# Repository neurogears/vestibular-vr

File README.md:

# vestibular-vr
Closed-loop VR setup for Rancz Lab

[Design Document](https://github.com/neurogears/vestibular-vr/blob/main/Design%20Documents/Vestibular%20VR%20Design%20Document.md)

### Acquisition Prerequisites

The following need to be installed on a fresh system in order to bootstrap the Bonsai environment correctly:

* Windows 10 or greater
* [Visual Studio Code](https://code.visualstudio.com/) (recommended for editing code scripts and git commits)
* [.NET 8.0 SDK](https://dotnet.microsoft.com/en-us/download/dotnet/8.0)
* [.NET Framework 4.7.2 Developer Pack](https://dotnet.microsoft.com/download/dotnet-framework/thank-you/net472-developer-pack-offline-installer) (required for intellisense when editing code scripts)
* [Git for Windows](https://gitforwindows.org/) (recommended for cloning and manipulating this repository)
* [Visual C++ Redistributable for Visual Studio 2012](https://www.microsoft.com/en-us/download/details.aspx?id=30679) (native dependency for OpenCV)
* [FTDI CDM Driver 2.12.28](https://www.ftdichip.com/Drivers/CDM/CDM21228_Setup.zip) (serial port drivers for HARP devices)
* [Spinnaker SDK 1.29.0.5](https://www.teledynevisionsolutions.com/support/support-center/software-firmware-downloads/iis/spinnaker-sdk-download/spinnaker-sdk--download-files) (device drivers for FLIR cameras, sign in required, look in the archived stable versions for 1.29.0.5)

### Setting up the Bonsai environment

To set up a Bonsai environment for running vestibular-vr, use the terminal to clone the repo into a local folder:

``` 
git clone https://github.com/neurogears/vestibular-vr.git
```

Now navigate into vestibular-vr/bonsai folder and run the `Setup.ps1` script (on Windows right-click > Run with powershell). Once all dependencies have been restored Bonsai can be launched in a local environment from the `.exe` in this folder.

### Session settings

Experiment parameters are based on a json schema (`schema.json` in the repo). Implementations of this schema are defined in `.yml` files provided by the user that are then loaded in the main Bonsai workflow to set up experiment parameters.

#### Working with schemas in Visual Studio Code
To create and edit schema implementations with full autcomplete and hinting, Visual Studio Code requires some extensions to be added:
* json (ZainChen.json)
* JSON Schema Validator (tberman.json-schema-validator)
* YAML (redhat.vscode-yaml)

#### Creating an experiment parameter file
To create an experiment parameter file based on the `schema`, create a new `.yml` file and add a reference to the `schema` at the top of the file

```
%YAML 1.1
---
# yaml-language-server: $schema=schema.json
```

The `schema` has two main groups of properties that define global experiment parameters, and block-specific parameters respectively, e.g.:

```
metadata:
  animalId: plimbo
  rootPath: D:/TrialLogicTestData/
  runGain: 0.0005

blocks: [
  &blockA
  {
    stimulus: {type: "grating"},
    totalRuntime: 20,
    runThreshold: 100,
    decayTimestep: 0.1,
    runThresholdDecay: -1,
    haltProbability: 0.5,
    haltProtocol: {
      minumumDelay: 0.1,
      randomDelay: 1.5,
      haltTime: 2,
      haltGain: 0
    }
  },
  &blockB
  {
    stimulus: {type: "cloud"},
    totalRuntime: 140,
    runThreshold: 200,
    decayTimestep: 0.1,
    runThresholdDecay: -1,
    haltProbability: 0.7,
    haltProtocol: {
      minumumDelay: 0.1,
      randomDelay: 0.5,
      haltTime: 0.5,
      haltGain: 0
    }
  },
  {<<: *blockA},
  {<<: *blockB}
]
```

The description of each parameter's effect on the Bonsai workflow, along with its type and default values are defined within `schema.json` itself. Note that where a parameter is not specifically set in the `.yml` the value will revert the default.

### Running an experiment
To run an experiment, run the Bonsai application from the local environment and open Main.bonsai. Use the property grid to select the desired experiment parameter `.yml` file.

### Gain settings
The `schema` has a number of gain settings that can be used to flexibly the define the relationship between real-time data sources (ball movement, encoder reading, file playback) and closed-loop outputs like visual field movement or motor movement. These gains are applied hierarchically with some affecting all calculations, and some defined per-block or per-source:

- `runGain` - global gain applied to all calculations
  - `blockGainModifier` - additional gain specific to a block
    - Visual: gains that contribute to visual field motion
      - `flowXToVisualGain` - gain applied to optical sensor X reading
      - `flowYToVisualGain` - gain applied to optical sensor Y reading
      - `rotaryToVisualGain` - gain applied to the rotary encoder reading
      - `playbackToVisualGain` - gain applied to the file playback data source
    - Motor: gains that contribute to motor motion
      - `flowXToMotorGain` - gain applied to optical sensor X reading
      - `flowYToMotorGain` - gain applied to optical sensor Y reading
      - `playbackToMotorGain` - gain applied to the file playback data source
  - `haltGain` - set as part of a `haltProtocol`. Applies a gain to all sources during a halt, block-specific.

We use the term 'procession' to describe the movement delta of the visual field or motor in response to an update from a data source (optical flow, playback etc.) on a given trial. Let `h` be a variable that describes whether a halt is currently happening (1 = halt happening, 0 = halt not happening), visual and motor processions are defined as:

```
visualProcession = (runGain * blockGainModifier) * (flowXToVisualGain*flowX + flowYToVisualGain*flowY + rotaryToVisualGain*encoder + playbackToVisualGain*playback) * (haltGain*h)
```
```
motorProcession = (runGain * blockGainModifier) * (flowXToMotorGain*flowX + flowYToMotorGain*flowY + playbackToVisualGain*playback) * (haltGain*h)
```

`motorProcession` is converted by the function `ToPulseInterval` to an immediate pulse interval command which is written to the motor. The conversion between this command and the speed of the motor is dependent on the hardware settings for pulse interval --> motor motion on the motor controller.
The relationship of `visualProcession` to visual field movement is dependent on the current visual stimulus being presented. For example for a gratings stimulus, the value represents the absolute phase angle of the gratings being shown. For a motion clouds stimulus, it represents the (wrapped) index of the motion cloud frame being shown.

Gains can be set to modify the contribution of a data source to procession, for example to specify a block where visual motion is only dependent on the X value of the flow sensor we can set:

```
# metadata
runGain: 0.0008 # represents final conversion from procession to visual angle
# block settings
blockGainModifier: 1 # block modifier does not scale input data sources
flowXToVisualGain: 1 # we want the X flow value to contribute
flowYToVisualGain: 0 # we don't want the Y flow value to contribute
rotaryToVisualGain: 0 # encoder reading should not contribute
playbackToVisualGain: 0 # playback source should not contribute
```

### Optical flow sensor smoothing

An average smoothing function is applied to the optical sensor reading. A `schema` parameter `flowSmoothing` is applied per-block which specifies a count of how many samples to smooth over, i.e. the length of the buffer to take an average, smoothed value from.

### Data logging
Data is logged according to the [Aeon.Acquisition](https://github.com/SainsburyWellcomeCentre/aeon_acquisition) format. Generally, data is grouped according to a folder named with a timestamp representing the start time of an experiment. Within this folder, data is organised by **device**, where a device may be a camera, Harp board, ONIX acquisition etc. For longer experiments, data is 'chunked' by hour such that the full raw data is split across multiple files to ensure no single file grows unmanageably large.

Within each device, data may be stored in a different format according to the device's data output. In general however, there will be a log of the raw data (e.g. camera frames, sensor readings) and a corresponding source of timestamps to allow for relating the data to the Harp clock. For a camera, this will take the form of a video file with the acquired camera frames, as well as a corresponding .csv file with paired Harp timestamps and camera frame indices. For a Harp device, this will take the form of a flat binary file organised by individual register, with the output of that register paired with a Harp timestamp.

As Harp files are saved as flat binary, it is recommended to use the device schema for that Harp device to parse the individual values and read the correct data type.

### Python environment

The following need to be installed once on a new system in order to analyze data:

 * [Visual Studio Code](https://code.visualstudio.com/) (recommended for editing code scripts and git commits)
 * A Conda distribution such as [Miniconda](https://docs.anaconda.com/free/miniconda/index.html)
 * [Python Extension for VS Code](https://marketplace.visualstudio.com/items?itemName=ms-python.python)
   * This extension needs to be made aware of the Conda installation. To do so, navigate to the extension settings. Under the section **Python: Conda Path**, enter the full path to the conda.bat executable. ([more info](https://stackoverflow.com/a/77615160/3312269).)
 * [Jupyter Extension for VS Code](https://marketplace.visualstudio.com/items?itemName=ms-toolsai.jupyter)

#### Create local Environment
1. Open the vestibular-vr folder in VS Code
2. `Ctrl+Shift+P` in VS Code > Python: Create Environment
   * Select Conda
   * Select Python 3.11 kernel
3. Ensure pip is upgraded:
 ```
 pip install --upgrade pip
 ```
4. From the terminal run `pip install -r requirements.txt`
5. Clone aeon_mecha into a separate directory 
 ```
 git clone https://github.com/SainsburyWellcomeCentre/aeon_mecha.git 
 ```
6. From the VS Code terminal, `cd` into the aeon_mecha directory and run:
 ```
 python -m pip install -e .
 ```

 ### SLEAP
 Follow the standard instructions for [installing SLEAP](https://sleap.ai/installation.html), [creating a project](https://sleap.ai/tutorials/new-project.html) and [labeling](https://sleap.ai/tutorials/initial-labeling.html). Ensure that you use training videos of the same pixel width and height that you will use for inference later. During training, ensure you select `single animal` as the training pipeline type, and that the image is converted to grayscale.

 After completing training, activate the sleap conda environment (if not already activated) and run:

 ```
sleap-export -m /model/folder/path
 ```

 to export the trained model to a format that can be used by Bonsai.

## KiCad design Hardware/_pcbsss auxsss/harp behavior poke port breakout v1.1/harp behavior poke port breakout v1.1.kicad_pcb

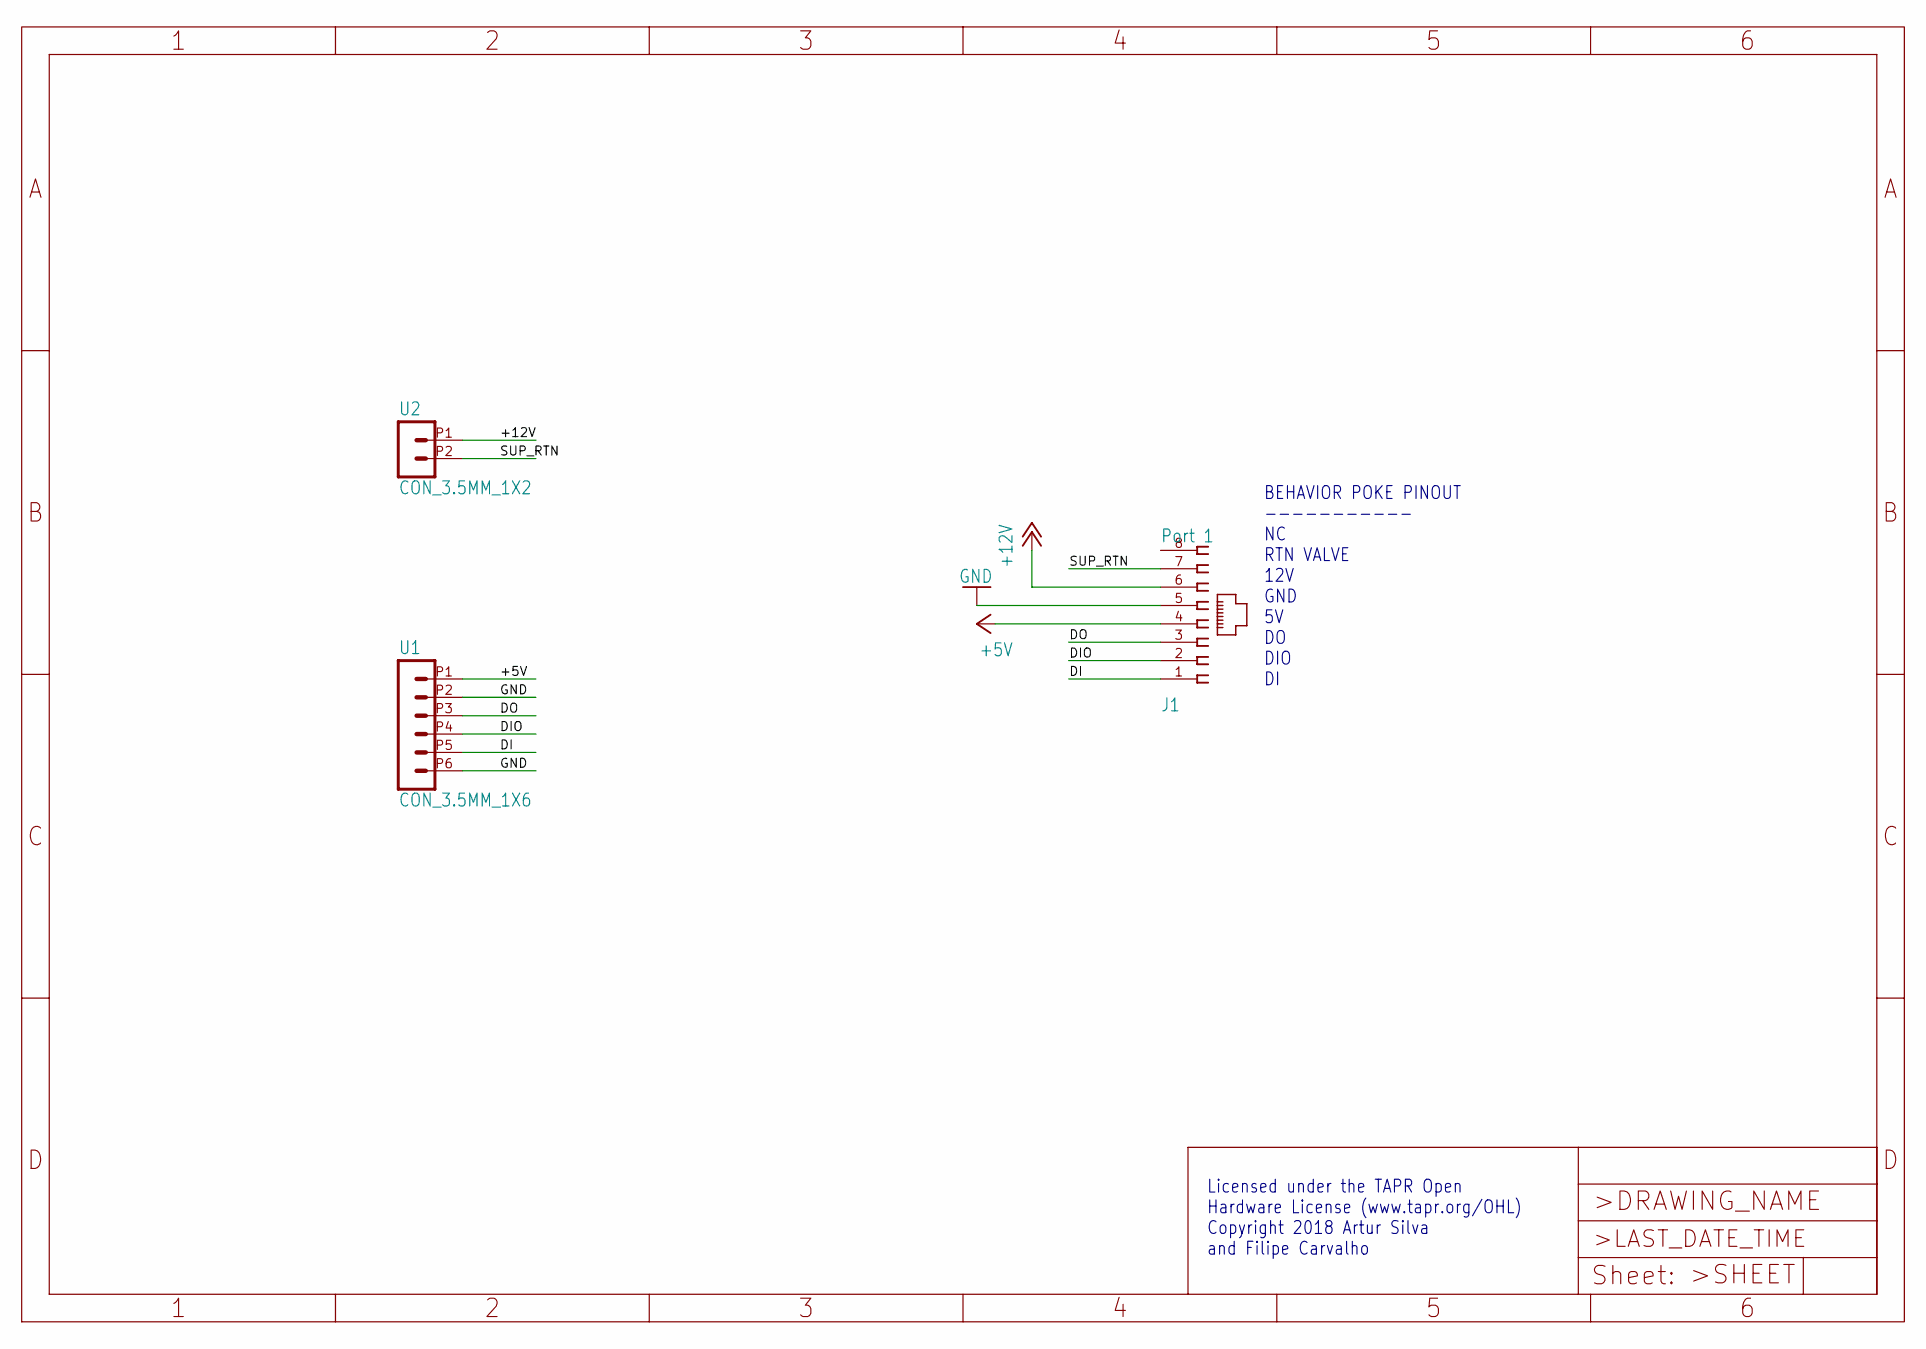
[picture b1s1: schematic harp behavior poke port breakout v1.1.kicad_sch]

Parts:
J1: Port 1; 520426-4
U1: CON_3.5MM_1X6
U2: CON_3.5MM_1X2

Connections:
+5V: J1.4, U1.P1 (1)
+12V: J1.6, U2.P1 (1)
DI: J1.1, U1.P5 (5)
DIO: J1.2, U1.P4 (4)
DO: J1.3, U1.P3 (3)
GND: J1.5, U1.P2 (2), U1.P6 (6)
SUP_RTN: J1.7, U2.P2 (2)

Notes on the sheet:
BEHAVIOR POKE PINOUT ----------- NC RTN VALVE 12V GND 5V DO DIO DI
Licensed under the TAPR Open Hardware License (www.tapr.org/OHL) Copyright 2018 Artur Silva and Filipe Carvalho

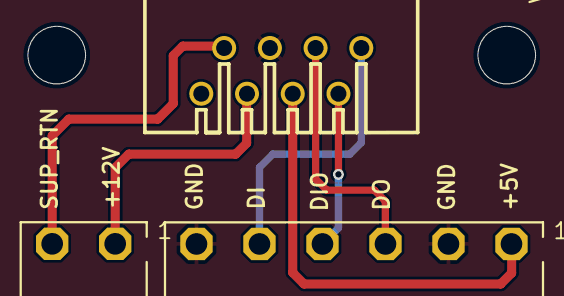
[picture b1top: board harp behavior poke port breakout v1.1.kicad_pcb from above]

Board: 2 copper layers, 6 parts (0 on the bottom side), 7 nets.

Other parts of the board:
@HOLE0, @HOLE1: (no value)
U$2: LOGO_8

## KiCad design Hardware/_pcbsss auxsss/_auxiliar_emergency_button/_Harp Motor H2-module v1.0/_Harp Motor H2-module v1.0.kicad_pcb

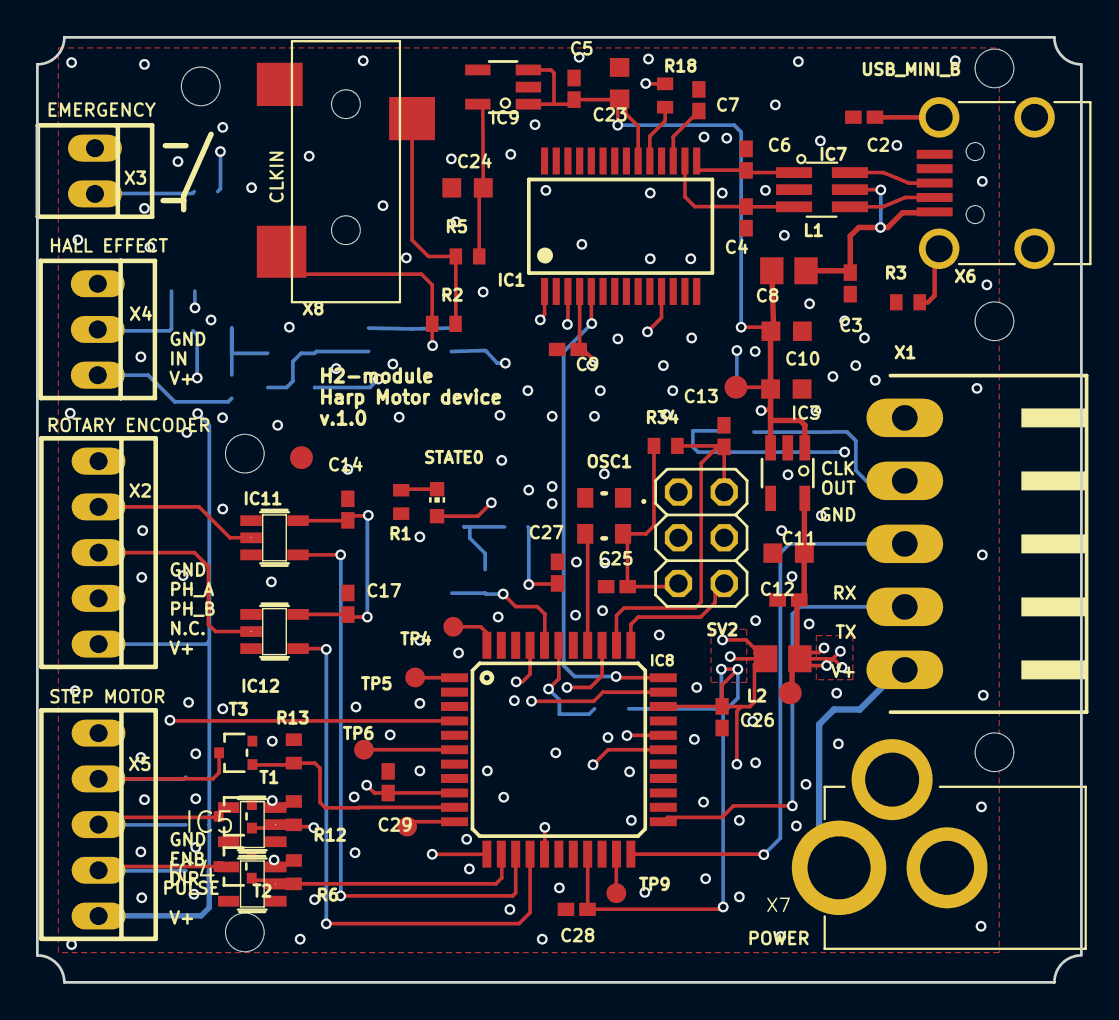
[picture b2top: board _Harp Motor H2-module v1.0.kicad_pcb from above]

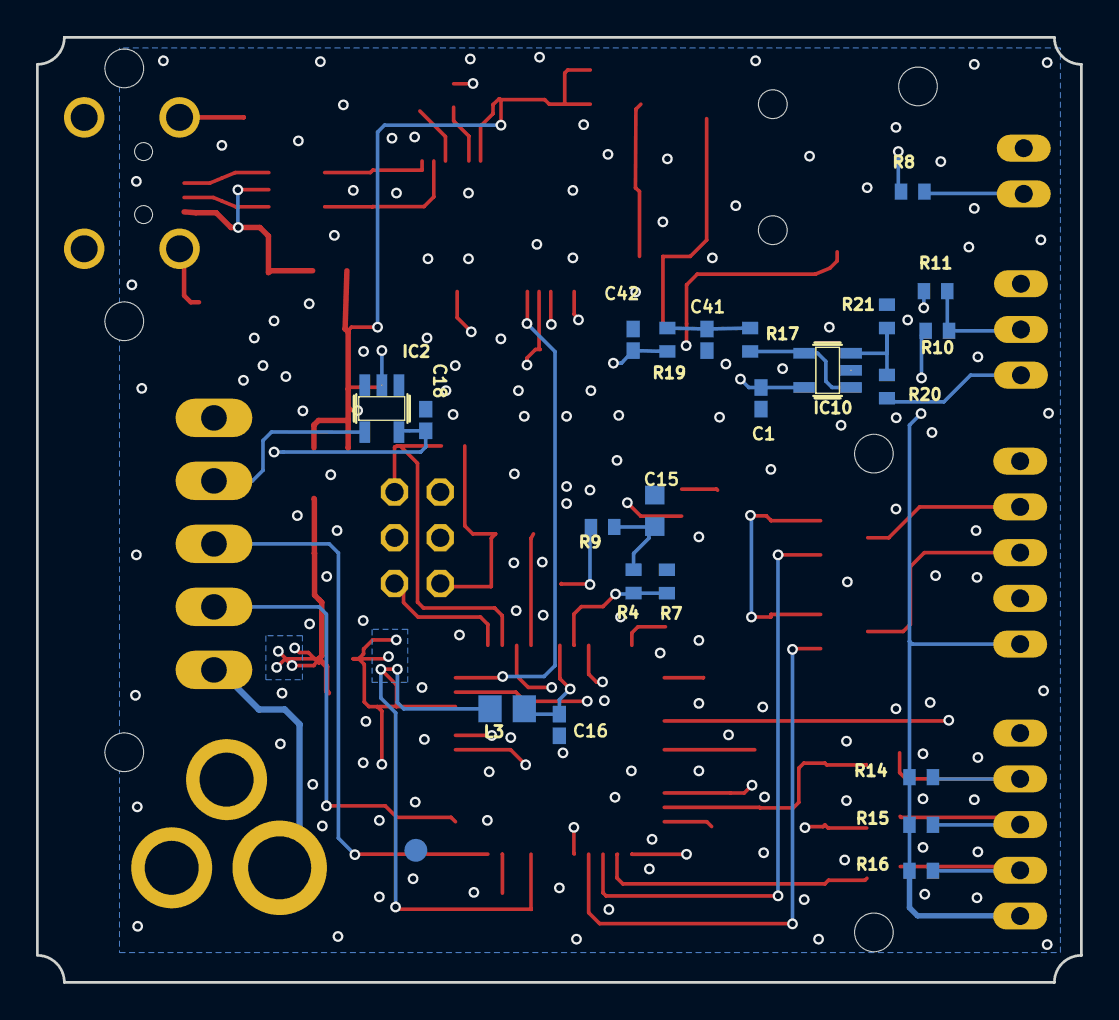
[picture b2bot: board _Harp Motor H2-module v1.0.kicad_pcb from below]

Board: 4 copper layers, 58.0 x 52.5 mm, 92 parts (23 on the bottom side), 54 nets.

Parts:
@HOLE0, @HOLE1, @HOLE2, @HOLE3, @HOLE4, @HOLE5: (no value)
C1, C3, C5, C7, C9, C12, C14, C16, C17, C18, C25, C26, C27, C28, C29: 100nF; C0402K
C2: 4.7nF; C0402K
C4, C6, C13: 47pF; C0402K
C8, C10, C11, C23, C24: 4.7uF; C0603K
C15: DNI 4.7uF; C0603K
C41, C42: 15nF 5%; C0402K
IC1: FT232RL; SSOP28
IC2, IC4, IC5, IC11, IC12: SN74LVC1G125DBVT; SOT23-5
IC3, IC9: LP5907MFX-3.3; TSOT23-5
IC7: USBLC6-2SC6; SOT23-6L
IC8: ATXMEGA32A4U; TQFP44
IC10: THS4281DBVT; SOT23-5
L1, L2, L3: 40R@100MHz; R0805
OSC1: OSCILLATOR; OSCILLATOR_3.2X2.5
R1: 330R; R0402
R2, R6, R8, R12, R13, R17, R18, R19, R34: 10k; R0402
R3: 1M; R0402
R4, R7, R14, R15, R16: DNI; R0402
R5: 10R; R0402
R9: DNI 100R; R0402
R10: DNI 0R; R0402
R11: 0R; R0402
R20: 24k; R0402
R21: 15k; R0402
STATE0: GREEN_LED; CHIP-LED0603
SV2: PINHD-2X3; 2X03
T1, T2, T3: DMG1012UW; SOT323
TP1, TP10, TP11, TP13: NO_COMPONENT; B1,27
TP4, TP5, TP6, TP8, TP9: NO_COMPONENT; TP11R
X1: 1x5 MAIN PLUG; 90G-5
X2, X5: 1x5 case; 22-23-2051
X3: 1x2 case; 22-23-2021
X4: 1x3 case; 22-23-2031
X6: USB_MINI_B; 240-0002-1
X7: DC_JACK2.1MM; DC_POWER_INPUT_2.1MM
X8: CLCK_JACK; 35RASMT2BHNTRX

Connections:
+3V3: C1.1, C9.1, C11.1, C12.1, C14.1, C17.1, C18.1, IC1.4, IC2.5, IC3.5, IC10.5, IC11.5, IC12.5, L2.2, R11.2, R18.1, TP1.TP
+5V: C5.1, C8.1, C10.1, C23.1, IC1.20, IC3.1, IC3.3, IC4.5, IC5.5, IC9.1, IC9.3, L1.1, R10.2, R14.2, R15.2, R16.2, TP13.TP, X2.5, X5.5
AREF: IC8.40, R4.1, R7.2
EMERGENCY_INPUT: IC8.4, R8.1, X3.2
FTDI_CTS: IC1.11, IC8.29
FTDI_RTS: IC1.3, IC8.28
FTDI_RXD: IC1.5, IC8.33
FTDI_TXD: IC1.1, IC8.32
GND: C1.2, C2.2, C3.2, C4.2, C5.2, C6.2, C7.2, C8.2, C9.2, C10.2, C11.2, C12.2, C13.2, C14.2, C15.2, C16.2, C17.2, C18.2, C23.2, C24.2, C25.2, C26.2, C27.2, C28.2, C29.2, C41.1, C42.1, IC1.7, IC1.18, IC1.21, IC1.25, IC1.26, IC2.1, IC2.3, IC3.2, IC4.1, IC4.3, IC5.1, IC5.3, IC7.P$2, IC8.8, IC8.18, IC8.30, IC8.38, IC8.42, IC9.2, IC10.2, IC11.1, IC11.3, IC12.1, IC12.3, OSC1.P$2, R1.1, R3.1, R6.1, R7.1, R12.1, R13.1, R21.1, SV2.6, T1.2, T2.2, T3.2, TP10.TP, TP11.TP, X1.5, X2.1, X3.1, X4.1, X5.1, X6.P$5, X7.P2, X7.P3, X8.5
HALL_EFFCT_IN: R20.2, X4.3
HARP_H2_CLOCK_OUT: IC2.4, X1.4
HARP_H2_RX: IC8.22, X1.3
HARP_H2_TX: IC8.23, X1.2
LED_STATE: IC8.36, STATE0.A
unnamed: R3.2, X6.SHIELD_4
unnamed: IC7.P$4, X6.P$2
unnamed: IC7.P$6, X6.P$3
unnamed: IC8.15, IC12.4
unnamed: C15.1, R4.2, R9.1
unnamed: C16.1, IC8.39, L3.1
unnamed: C41.2, R17.2, R19.1
unnamed: IC10.1, IC10.4, R17.1
unnamed: R1.2, STATE0.C
unnamed: IC10.3, R20.1, R21.2
unnamed: IC8.44, TP4.TP
unnamed: IC8.1, TP5.TP
unnamed: IC8.6, TP6.TP
unnamed: R10.1, R11.1, X4.2
unnamed: C2.1, X6.SHIELD_3
unnamed: IC12.2, X2.3
unnamed: IC8.11, TP8.TP
unnamed: IC8.21, TP9.TP
unnamed: IC11.2, X2.2
unnamed: C7.1, IC1.17
unnamed: R2.2, R5.2, X8.1
unnamed: C24.1, IC9.5, R5.1
unnamed: IC1.19, R18.2
OSC2: IC8.37, OSC1.P$3
PDI_CLK: C13.1, IC8.35, R34.1, SV2.5
PDI_DATA: IC8.34, SV2.1
STEP_DIRECTION: R15.1, T1.3, X5.3
STEP_ENABLE: R14.1, T3.3, X5.2
STEP_PULSE: IC4.4, R16.1, T2.3, X5.4
USBDM: C4.1, IC1.16, IC7.P$3
USBDP: C6.1, IC1.15, IC7.P$1
USB_POWER: C3.1, IC7.P$5, L1.2, X6.P$1
U_CLOCK_IN: IC2.2, IC8.12, R2.1, X8.4
U_ENCODER_B_PHASE: IC8.14, IC11.4
U_HALL_EFFCT_IN: C42.2, IC8.41, R19.2
U_STEP_DIRECTION: IC5.2, IC8.16, R12.2, T1.1
U_STEP_ENABLE: IC8.10, R13.2, T3.1
U_STEP_PULSE: IC4.2, IC8.13, R6.2, T2.1
V+: C25.1, C26.1, C27.1, C28.1, C29.1, IC8.9, IC8.19, IC8.31, L2.1, L3.2, OSC1.P$4, R8.2, R9.2, R34.2, SV2.2
VDD: X1.1, X7.P1

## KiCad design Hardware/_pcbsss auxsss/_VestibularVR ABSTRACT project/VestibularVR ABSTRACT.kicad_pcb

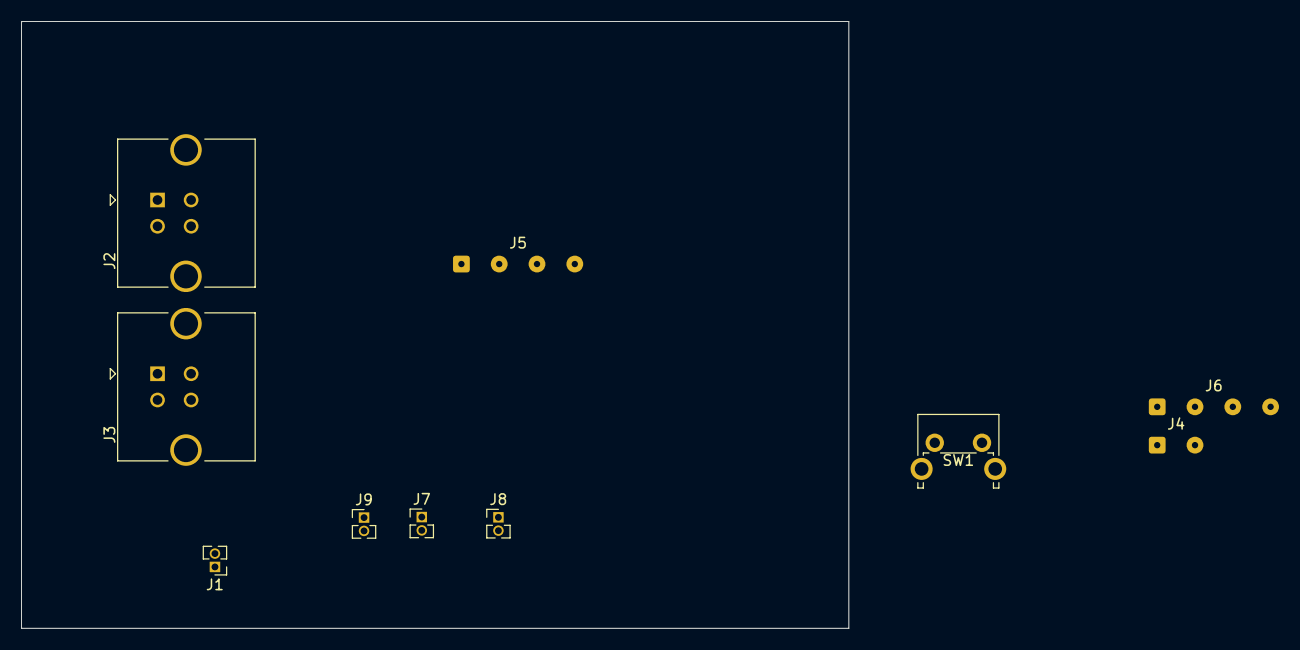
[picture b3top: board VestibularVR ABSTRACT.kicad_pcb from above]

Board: 2 copper layers, 78.8 x 57.8 mm, 10 parts (0 on the bottom side), 4 nets, no tracks yet.

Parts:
J1, J7, J8, J9: Conn_01x02_Female; PinHeader_1x02_P1.27mm_Vertical
J2, J3: USB_B; USB_B_TE_5787834_Vertical
J4: Conn_01x02_Female; SolderWire-0.1sqmm_1x02_P3.6mm_D0.4mm_OD1mm
J5, J6: Conn_01x04_Male; SolderWire-0.1sqmm_1x04_P3.6mm_D0.4mm_OD1mm
SW1: SW_Push_Open; SW_Tactile_SPST_Angled_PTS645Vx83-2LFS

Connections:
+3.3V: J7.2, J8.1, J9.1, J9.2
GNDD: J2.4 (GND), J2.5 (Shield), J3.4 (GND), J3.5 (Shield)
USB2_data+: J3.3 (D+), J5.3
USB2_data-: J3.2 (D-), J5.2

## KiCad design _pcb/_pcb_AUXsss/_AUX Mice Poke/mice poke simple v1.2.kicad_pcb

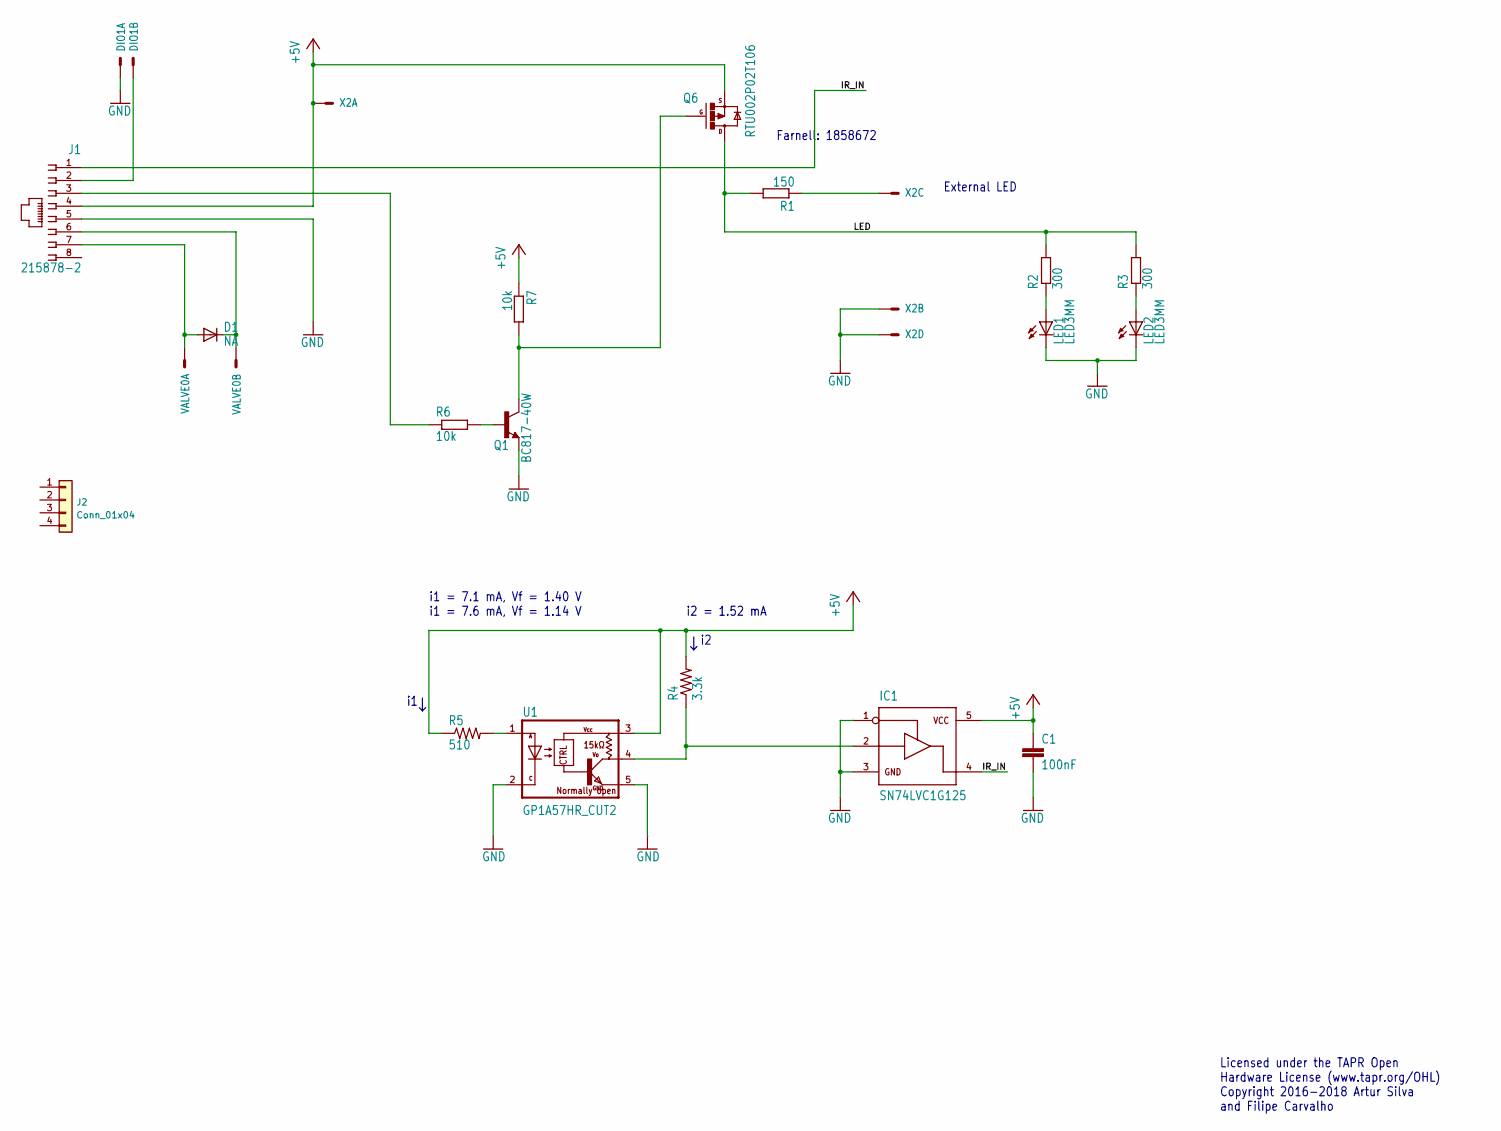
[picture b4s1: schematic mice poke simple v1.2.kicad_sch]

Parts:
C1: 100nF; C0402
D1: NA; SOD323-R
DIO1: 22-23-2021
IC1: SN74LVC1G125; SOT23-5
J1: 215878-2
J2: Conn_01x04; PinHeader_1x04_P1.27mm_Vertical
LED1, LED2: LED3MM
Q1: BC817-40W; SOT323-BEC
Q6: RTU002P02T106; SOT323
R1: 150; R0402
R2, R3: 300; R0402
R4: 3.3k; R0402
R5: 510; R0402
R6, R7: 10k; R0402
U1: GP1A57HR_CUT2
VALVE0: 22-23-2021
X2: 22-23-2041

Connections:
+5V: C1.1, IC1.5, J1.4, Q6.1 (S), R4.2, R5.1, R7.1, U1.3 (VCC), X2.1 (S)
/IR_IN: IC1.4, J1.1
/LED: Q6.3 (D), R1.2, R2.2, R3.2
GND: C1.2, DIO1.1 (S), IC1.1, IC1.3, J1.5, LED1.K (C), LED2.K (C), Q1.E, U1.2 (C), U1.5 (GND), X2.2 (S), X2.4 (S)
unnamed: D1.A, J1.7, VALVE0.1 (S)
unnamed: D1.C, J1.6, VALVE0.2 (S)
unnamed: DIO1.2 (S), J1.2
unnamed: IC1.2, R4.1, U1.4 (VO)
unnamed: J1.3, R6.1
unnamed: LED1.A, R2.1
unnamed: LED2.A, R3.1
unnamed: Q1.B, R6.2
unnamed: Q1.C, Q6.2 (G), R7.2
unnamed: R1.1, X2.3 (S)
unnamed: R5.2, U1.1 (A)

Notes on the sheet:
i1 = 7.1 mA, Vf = 1.40 V i1 = 7.6 mA, Vf = 1.14 V
Licensed under the TAPR Open Hardware License (www.tapr.org/OHL) Copyright 2016-2018 Artur Silva and Filipe Carvalho
External LED
i2 = 1.52 mA
Farnell: 1858672

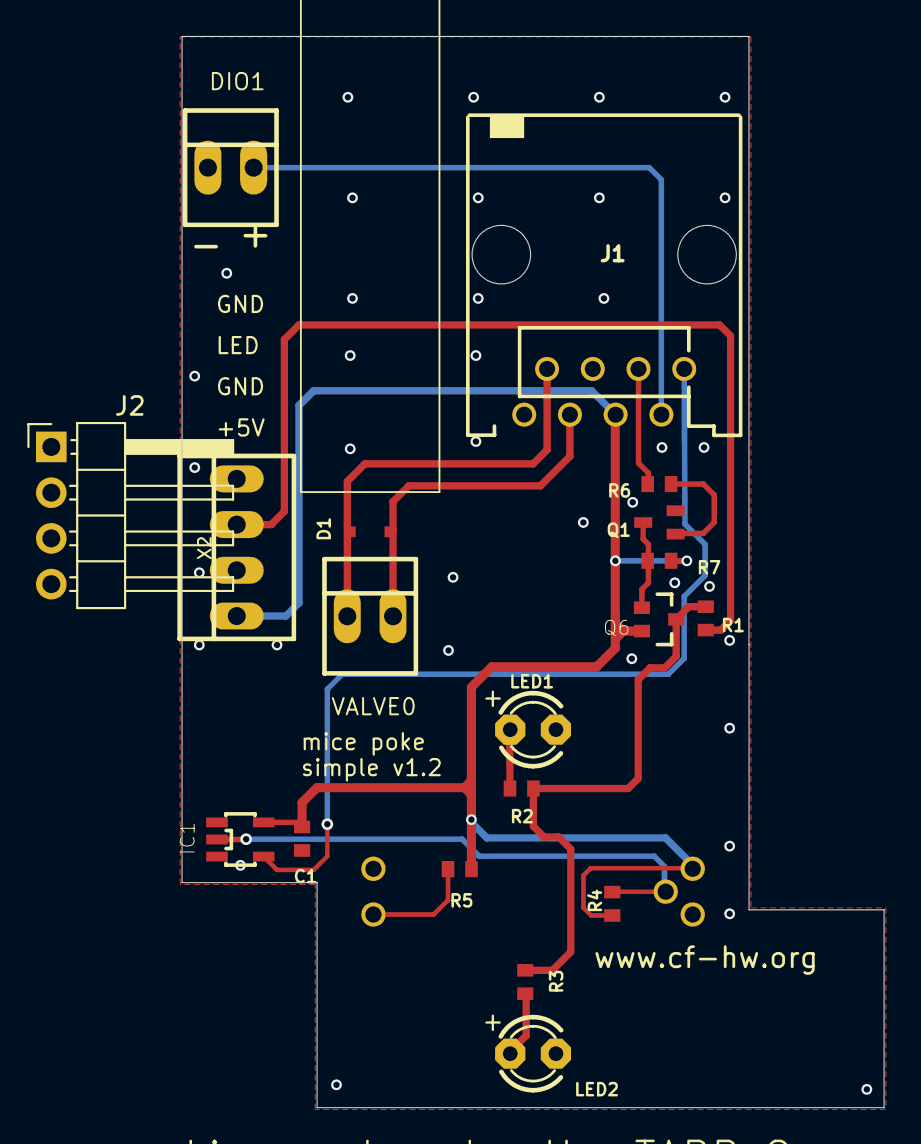
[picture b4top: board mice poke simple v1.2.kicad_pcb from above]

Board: 2 copper layers, 39.0 x 59.5 mm, 20 parts (1 on the bottom side), 15 nets.

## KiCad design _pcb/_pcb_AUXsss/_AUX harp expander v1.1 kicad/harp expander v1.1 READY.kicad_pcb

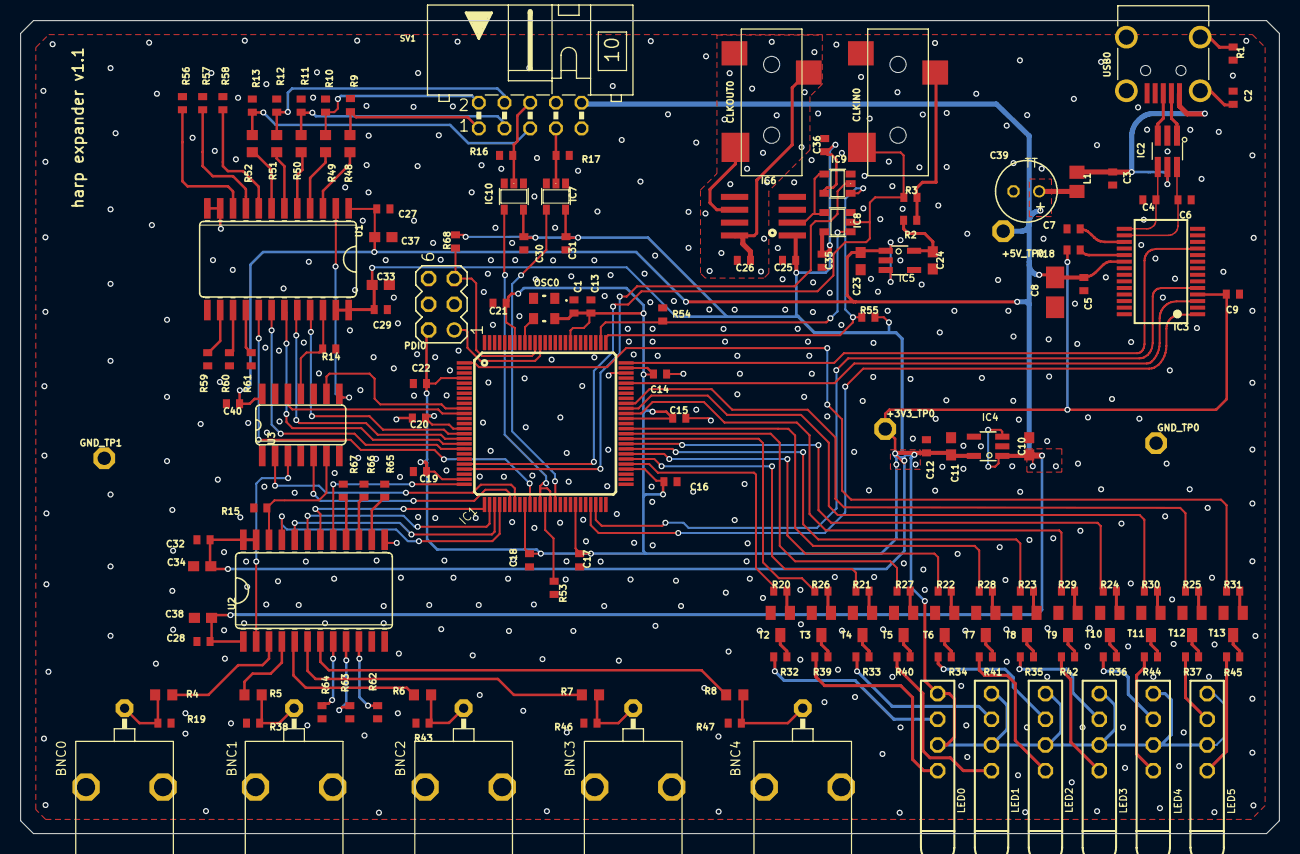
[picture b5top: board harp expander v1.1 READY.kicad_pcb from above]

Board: 2 copper layers, 124.5 x 80.4 mm, 155 parts (0 on the bottom side), 132 nets.

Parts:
+3V3_TP0, +5V_TP0: TPPAD1-13; P1-13
BNC0, BNC1, BNC2, BNC3, BNC4: BNC plug; 0731000105
C1, C3, C5, C7, C9, C12, C13, C14, C15, C16, C17, C18, C19, C20, C21, C22, C25, C26, C27, C28, C29, C30, C31, C32, C35, C36, C40: 100nF; C0402
C2: 4.7nF; C0402
C4, C6: 47pF; C0402
C8: 4.7uF; A_3216-18W
C10, C11, C23, C24, C33, C34, C37, C38: 4.7uF; C0603
C39: 100u 25V; TT2D6
CLKIN0: CLCK_JACK; 35RASMT2BHNTRX
CLKOUT0: CLCK_JACK; 35RASMT2BHNTRX
GND_TP0, GND_TP1: TPPAD1-13; P1-13
IC1: XMEGA-A1TQFP; TQFP100
IC2: USBLC6-2SC6; SOT23-6L
IC3: FT232RL; SSOP28
IC4, IC5: TLV70033DDCR; TSOT23-5
IC6: SI8610BC-B-IS; SO-08
IC7, IC8, IC9, IC10: SN74LVC1G125DBVT; SOT23-5
L1: 40R@100MHz; R0805
LED0, LED1, LED2, LED3, LED4, LED5: 569-0112-100; 569-011X-X00_LED_ARRAY
OSC0: Oscillator; OSCILLATOR_3.2X2.5
PDI0: PROG HEADER; MA03-2
R1: 1M; R0402
R2: 10R; R0402
R3, R9, R10, R11, R12, R13, R14, R15, R16, R17, R18, R19, R38, R43, R46, R47, R53, R54, R55, R56, R57, R58, R59, R60, R61, R62, R63, R64, R65, R66, R67: 10k; R0402
R4, R5, R6, R7, R8, R48, R49, R50, R51, R52: 100R; R0603
R20, R21, R22, R23, R24, R25, R26, R27, R28, R29, R30, R31: 1k; R0402
R32, R33, R34, R35, R36, R37, R39, R40, R41, R42, R44, R45: 330R; R0402
R68: 10k DNI; R0402
SV1: I/O Header; ML10L
T2, T3, T4, T5, T6, T7, T8, T9, T10, T11, T12, T13: BC850; SOT23
U1, U2: 744245X; SO24L
U3: 74HCT125SO14; SO14
USB0: mini USB; 240-0002-1

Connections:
5VUSB: C3.1, IC2.P$5, L1.2, USB0.P$1
+3V3: +3V3_TP0.TP, C1.1, C9.1, C11.1, C12.1, C13.1, C14.1, C15.1, C16.1, C17.1, C18.1, C19.1, C20.1, C21.1, C22.1, C25.1, C29.1, C30.1, C31.1, C32.1, C33.1, C34.1, C35.1, C36.1, IC1.4, IC1.14, IC1.24, IC1.34, IC1.44, IC1.54, IC1.64, IC1.74, IC1.83, IC1.94, IC3.4, IC4.5, IC6.1, IC7.5, IC8.5, IC9.5, IC10.5, LED0.A1, LED0.A2, LED1.A1, LED1.A2, LED2.A1, LED2.A2, LED3.A1, LED3.A2, LED4.A1, LED4.A2, LED5.A1, LED5.A2, OSC0.P$4, PDI0.2, R18.1, R55.2, R68.2, U1.23, U1.24, U2.23, U2.24
+5V: +5V_TP0.TP, C5.1, C8.+, C10.1, C23.1, C27.1, C28.1, C37.1, C38.1, C39.+, C40.1, IC3.20, IC4.1, IC4.3, IC5.1, IC5.3, L1.1, SV1.10, U1.1, U2.1, U3.14
AUX_IN0_UC: IC1.37, IC1.39, IC10.4
AUX_IN1_UC: IC1.40, IC7.4
CLOCK_IN: CLKIN0.4, IC1.21, IC8.2, R3.2
CLOCK_OUT: IC1.22, IC9.2
FTDI_CTS: IC1.75, IC3.11
FTDI_RTS: IC1.71, IC3.3
FTDI_RXD: IC1.48, IC3.5
FTDI_TXD: IC1.47, IC3.1
GND: BNC0.2, BNC0.3, BNC1.2, BNC1.3, BNC2.2, BNC2.3, BNC3.2, BNC3.3, BNC4.2, BNC4.3, C1.2, C2.2, C3.2, C4.2, C5.2, C6.2, C7.2, C8.-, C9.2, C10.2, C11.2, C12.2, C13.2, C14.2, C15.2, C16.2, C17.2, C18.2, C19.2, C20.2, C21.2, C22.2, C23.2, C24.2, C25.2, C27.2, C28.2, C29.2, C30.2, C31.2, C32.2, C33.2, C34.2, C35.2, C36.2, C37.2, C38.2, C39.-, C40.2, CLKIN0.5, GND_TP0.TP, GND_TP1.TP, IC1.3, IC1.13, IC1.23, IC1.33, IC1.43, IC1.50, IC1.53, IC1.63, IC1.73, IC1.84, IC1.93, IC2.P$2, IC3.7, IC3.18, IC3.21, IC3.25, IC3.26, IC4.2, IC5.2, IC6.4, IC7.1, IC7.3, IC8.3, IC9.3, IC10.1, IC10.3, OSC0.P$2, PDI0.6, R1.2, R9.2, R10.2, R11.2, R12.2, R13.2, R14.1, R15.1, R16.2, R17.2, R19.1, R38.1, R43.1, R46.1, R47.1, R53.2, R54.2, R56.2, R57.2, R58.2, R59.2, R60.2, R61.2, R62.2, R63.2, R64.2, R65.2, R66.2, R67.2, SV1.9, T2.2, T3.2, T4.2, T5.2, T6.2, T7.2, T8.2, T9.2, T10.2, T11.2, T12.2, T13.2, U1.11, U1.12, U1.13, U2.11, U2.12, U2.13, U3.1, U3.4, U3.7, U3.10, U3.13, USB0.P$5
GND_ISO: C26.2, CLKOUT0.5, IC6.5
IO0_UC: IC1.29, U2.21
IO1: BNC1.1, R5.1, R38.2
IO1_UC: IC1.28, U2.20
IO2: BNC2.1, R6.1, R43.2
IO2_UC: IC1.27, U2.19
IO3: BNC3.1, R7.1, R46.2
IO3_UC: IC1.26, U2.18
IO4: BNC4.1, R8.1, R47.2
IO4_UC: IC1.25, U2.17
IO5: R9.1, R48.1, SV1.1
IO6: R10.1, R49.1, SV1.2
IO7: R11.1, R50.1, SV1.3
IO8: R12.1, R51.1, SV1.4
IO9: R13.1, R52.1, SV1.5
LED_I0: IC1.55, R20.1
LED_I1: IC1.56, R21.1
LED_I2: IC1.57, R22.1
LED_I3: IC1.58, R23.1
LED_I4: IC1.59, R24.1
LED_I5: IC1.60, R26.1
LED_I6: IC1.61, R27.1
LED_I7: IC1.62, R28.1
LED_I8: IC1.65, R29.1
LED_I9: IC1.66, R30.1
LED_PWR: IC1.67, R25.1
unnamed: R24.2, T10.1
unnamed: CLKOUT0.4, IC6.6
unnamed: R20.2, T2.1
unnamed: LED0.C2, R32.1
unnamed: C26.1, CLKOUT0.1, IC6.8
unnamed: R36.2, T10.3
unnamed: R32.2, T2.3
unnamed: R26.2, T3.1
unnamed: R22.2, T6.1
unnamed: R39.2, T3.3
unnamed: R21.2, T4.1
unnamed: LED3.C1, R42.1
unnamed: R33.2, T4.3
unnamed: R27.2, T5.1
unnamed: R34.2, T6.3
unnamed: R40.2, T5.3
unnamed: LED3.C2, R35.1
unnamed: R28.2, T7.1
unnamed: R41.2, T7.3
unnamed: R23.2, T8.1
unnamed: R35.2, T8.3
unnamed: R29.2, T9.1
unnamed: R42.2, T9.3
unnamed: LED1.C2, R33.1
unnamed: LED2.C2, R34.1
unnamed: LED1.C1, R40.1
unnamed: LED2.C1, R41.1
unnamed: R30.2, T11.1
unnamed: LED0.C1, R39.1
unnamed: C7.1, IC3.17
unnamed: IC2.P$1, USB0.P$2
unnamed: CLKIN0.1, R2.2, R3.1
unnamed: C24.1, IC5.5, R2.1
unnamed: IC6.2, IC8.4, IC9.4
unnamed: R44.2, T11.3
unnamed: IC2.P$3, USB0.P$3
unnamed: IC3.19, R18.2
unnamed: BNC0.1, R4.1, R19.2
unnamed: R25.2, T12.1
unnamed: R37.2, T12.3
unnamed: IC1.15, U1.21
unnamed: R31.2, T13.1
unnamed: IC1.16, U1.20
unnamed: IC1.17, U1.19
unnamed: C2.1, USB0.SHIELD_4
unnamed: R45.2, T13.3
unnamed: R1.1, USB0.SHIELD_1
unnamed: LED5.C1, R45.1
unnamed: LED5.C2, R37.1
unnamed: LED4.C2, R36.1
unnamed: LED4.C1, R44.1
unnamed: IC1.18, U1.18
unnamed: IC1.35, U1.17
unnamed: R14.2, U1.22, U3.11
unnamed: R49.2, U1.4
unnamed: R50.2, U1.5
unnamed: R51.2, U1.6
unnamed: R52.2, U1.7
unnamed: R4.2, U2.3
unnamed: R5.2, U2.4
unnamed: R6.2, U2.5
unnamed: R7.2, U2.6
unnamed: R8.2, U2.7
unnamed: IC10.2, R16.1, SV1.6
unnamed: IC7.2, R17.1, SV1.7
unnamed: R15.2, U2.22, U3.6
unnamed: U2.2, U3.3
unnamed: U1.2, U3.8
unnamed: R48.2, U1.3
unnamed: IC1.38, R53.1
unnamed: IC1.77, IC8.1, R54.1
unnamed: IC1.76, IC9.1, R55.1
unnamed: IC1.32, U3.2
unnamed: IC1.31, U3.5
unnamed: IC1.10, U3.9
unnamed: IC1.11, U3.12
unnamed: R61.1, U1.16
unnamed: R60.1, U1.15
unnamed: R59.1, U1.14
unnamed: R56.1, U1.10
unnamed: R57.1, U1.9
unnamed: R58.1, U1.8
unnamed: R62.1, U2.10
unnamed: R63.1, U2.9
unnamed: R64.1, U2.8
unnamed: R66.1, U2.15
unnamed: R67.1, U2.16
unnamed: R65.1, U2.14
OSC1: IC1.92, OSC0.P$3
PDI_CLK: IC1.90, PDI0.5, R68.1
PDI_DATA: IC1.89, PDI0.1
STATE: IC1.1, R31.1
USBDM: C6.1, IC2.P$6, IC3.16
USBDP: C4.1, IC2.P$4, IC3.15
